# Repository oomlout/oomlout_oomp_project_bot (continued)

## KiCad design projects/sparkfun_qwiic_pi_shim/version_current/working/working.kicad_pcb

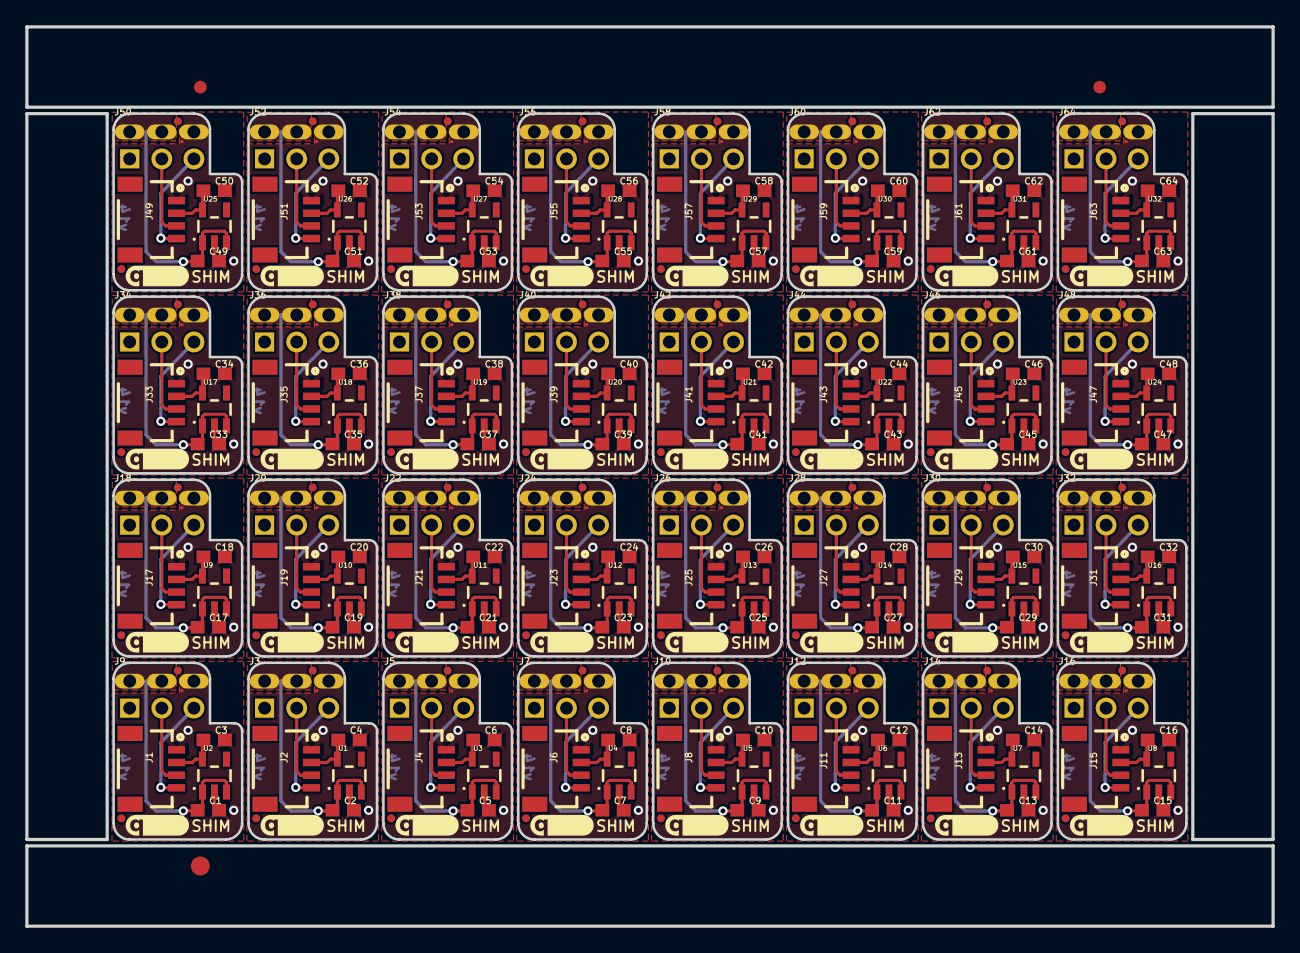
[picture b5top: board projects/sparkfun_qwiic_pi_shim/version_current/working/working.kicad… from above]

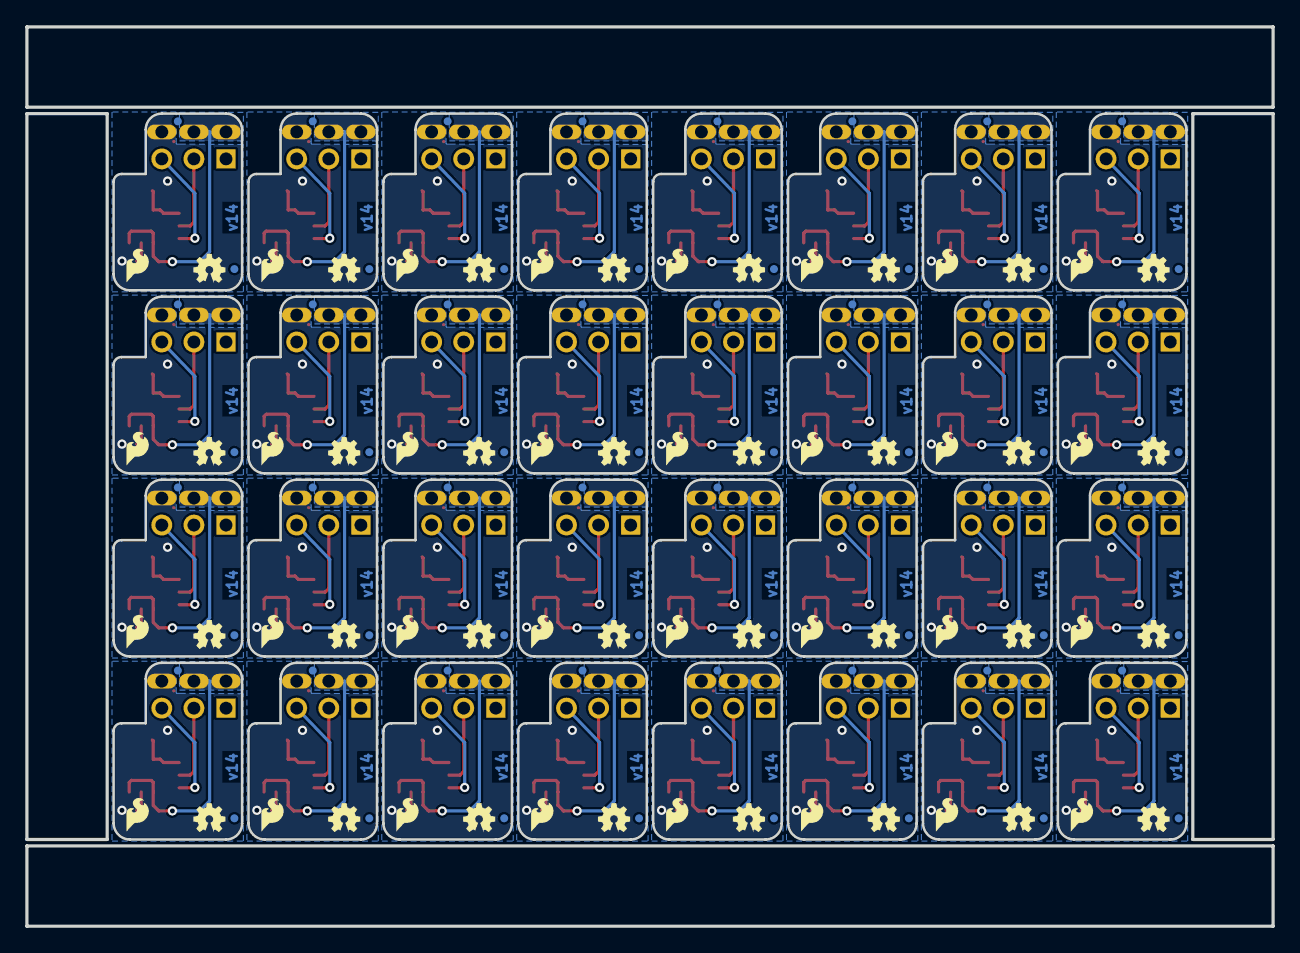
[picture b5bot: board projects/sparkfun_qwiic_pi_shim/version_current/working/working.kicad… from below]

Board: 2 copper layers, 98.6 x 71.1 mm, 387 parts (128 on the bottom side), 160 nets.

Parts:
C1, C2, C3, C4, C5, C6, C7, C8, C9, C10, C11, C12, C13, C14, C15, C16, C17, C18, C19, C20, C21, C22, C23, C24, C25, C26, C27, C28, C29, C30, C31, C32, C33, C34, C35, C36, C37, C38, C39, C40, C41, C42, C43, C44, C45, C46, C47, C48, C49, C50, C51, C52, C53, C54, C55, C56, C57, C58, C59, C60, C61, C62, C63, C64: 1.0uF; 0603
E$1, E$2: FIDUCIAL-1X2
E$3: FIDUCIAL-1.5X3
FD1, FD2, FD3, FD4, FD5, FD6, FD7, FD8, FD9, FD10, FD11, FD12, FD13, FD14, FD15, FD16, FD17, FD18, FD19, FD20, FD21, FD22, FD23, FD24, FD25, FD26, FD27, FD28, FD29, FD30, FD31, FD32, FD33, FD34, FD35, FD36, FD37, FD38, FD39, FD40, FD41, FD42, FD43, FD44, FD45, FD46, FD47, FD48, FD49, FD50, FD51, FD52, FD53, FD54, FD55, FD56, FD57, FD58, FD59, FD60, FD61, FD62, FD63, FD64, FD65, FD66, FD67, FD68, FD69, FD70, FD71, FD72, FD73, FD74, FD75, FD76, FD77, FD78, FD79, FD80, FD81, FD82, FD83, FD84, FD85, FD86, FD87, FD88, FD89, FD90, FD91, FD92, FD93, FD94, FD95, FD96, FD97, FD98, FD99, FD100, FD101, FD102, FD103, FD104, FD105, FD106, FD107, FD108, FD109, FD110, FD111, FD112, FD113, FD114, FD115, FD116, FD117, FD118, FD119, FD120, FD121, FD122, FD123, FD124, FD125, FD126, FD127, FD128: FIDUCIALUFIDUCIAL; FIDUCIAL-MICRO
J1, J2, J4, J6, J8, J11, J13, J15, J17, J19, J21, J23, J25, J27, J29, J31, J33, J35, J37, J39, J41, J43, J45, J47, J49, J51, J53, J55, J57, J59, J61, J63: Qwiic Right Angle; 1X04_1MM_RA
J3, J5, J7, J9, J10, J12, J14, J16, J18, J20, J22, J24, J26, J28, J30, J32, J34, J36, J38, J40, J42, J44, J46, J48, J50, J52, J54, J56, J58, J60, J62, J64: SPARKFUN-CONNECTORS_2X3-NS_PISHIM_LOCKING_SLOTS-4MILS
LOGO1, LOGO2, LOGO3, LOGO4, LOGO5, LOGO6, LOGO7, LOGO8, LOGO9, LOGO10, LOGO11, LOGO12, LOGO13, LOGO14, LOGO15, LOGO16, LOGO17, LOGO18, LOGO19, LOGO20, LOGO21, LOGO22, LOGO23, LOGO24, LOGO25, LOGO26, LOGO27, LOGO28, LOGO29, LOGO30, LOGO31, LOGO32: OSHW-LOGOMINI; OSHW-LOGO-MINI
U1, U2, U3, U4, U5, U6, U7, U8, U9, U10, U11, U12, U13, U14, U15, U16, U17, U18, U19, U20, U21, U22, U23, U24, U25, U26, U27, U28, U29, U30, U31, U32: 3.3V/600mA; SOT23-5
U$1, U$2, U$5, U$7, U$9, U$11, U$13, U$15, U$17, U$19, U$21, U$23, U$25, U$27, U$29, U$31, U$33, U$35, U$37, U$39, U$41, U$43, U$45, U$47, U$49, U$51, U$53, U$55, U$57, U$59, U$61, U$63: SFE_LOGO_FLAME.1_INCH; SFE_LOGO_FLAME_.1
U$3, U$4, U$6, U$8, U$10, U$12, U$14, U$16, U$18, U$20, U$22, U$24, U$26, U$28, U$30, U$32, U$34, U$36, U$38, U$40, U$42, U$44, U$46, U$48, U$50, U$52, U$54, U$56, U$58, U$60, U$62, U$64: QWIIC_5MM

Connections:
3.3V: C3.1, J1.2, U2.5
3.3V1: C4.1, J2.2, U1.5
3.3V2: C6.1, J4.2, U3.5
3.3V3: C8.1, J6.2, U4.5
3.3V4: C10.1, J8.2, U5.5
3.3V5: C12.1, J11.2, U6.5
3.3V6: C14.1, J13.2, U7.5
3.3V7: C16.1, J15.2, U8.5
3.3V8: C18.1, J17.2, U9.5
3.3V9: C20.1, J19.2, U10.5
3.3V10: C22.1, J21.2, U11.5
3.3V11: C24.1, J23.2, U12.5
3.3V12: C26.1, J25.2, U13.5
3.3V13: C28.1, J27.2, U14.5
3.3V14: C30.1, J29.2, U15.5
3.3V15: C32.1, J31.2, U16.5
3.3V16: C34.1, J33.2, U17.5
3.3V17: C36.1, J35.2, U18.5
3.3V18: C38.1, J37.2, U19.5
3.3V19: C40.1, J39.2, U20.5
3.3V20: C42.1, J41.2, U21.5
3.3V21: C44.1, J43.2, U22.5
3.3V22: C46.1, J45.2, U23.5
3.3V23: C48.1, J47.2, U24.5
3.3V24: C50.1, J49.2, U25.5
3.3V25: C52.1, J51.2, U26.5
3.3V26: C54.1, J53.2, U27.5
3.3V27: C56.1, J55.2, U28.5
3.3V28: C58.1, J57.2, U29.5
3.3V29: C60.1, J59.2, U30.5
3.3V30: C62.1, J61.2, U31.5
3.3V31: C64.1, J63.2, U32.5
5V: C1.1, J9.2, J9.4, U2.1, U2.3
5V1: C2.1, J3.2, J3.4, U1.1, U1.3
5V2: C5.1, J5.2, J5.4, U3.1, U3.3
5V3: C7.1, J7.2, J7.4, U4.1, U4.3
5V4: C9.1, J10.2, J10.4, U5.1, U5.3
5V5: C11.1, J12.2, J12.4, U6.1, U6.3
5V6: C13.1, J14.2, J14.4, U7.1, U7.3
5V7: C15.1, J16.2, J16.4, U8.1, U8.3
5V8: C17.1, J18.2, J18.4, U9.1, U9.3
5V9: C19.1, J20.2, J20.4, U10.1, U10.3
5V10: C21.1, J22.2, J22.4, U11.1, U11.3
5V11: C23.1, J24.2, J24.4, U12.1, U12.3
5V12: C25.1, J26.2, J26.4, U13.1, U13.3
5V13: C27.1, J28.2, J28.4, U14.1, U14.3
5V14: C29.1, J30.2, J30.4, U15.1, U15.3
5V15: C31.1, J32.2, J32.4, U16.1, U16.3
5V16: C33.1, J34.2, J34.4, U17.1, U17.3
5V17: C35.1, J36.2, J36.4, U18.1, U18.3
5V18: C37.1, J38.2, J38.4, U19.1, U19.3
5V19: C39.1, J40.2, J40.4, U20.1, U20.3
5V20: C41.1, J42.2, J42.4, U21.1, U21.3
5V21: C43.1, J44.2, J44.4, U22.1, U22.3
5V22: C45.1, J46.2, J46.4, U23.1, U23.3
5V23: C47.1, J48.2, J48.4, U24.1, U24.3
5V24: C49.1, J50.2, J50.4, U25.1, U25.3
5V25: C51.1, J52.2, J52.4, U26.1, U26.3
5V26: C53.1, J54.2, J54.4, U27.1, U27.3
5V27: C55.1, J56.2, J56.4, U28.1, U28.3
5V28: C57.1, J58.2, J58.4, U29.1, U29.3
5V29: C59.1, J60.2, J60.4, U30.1, U30.3
5V30: C61.1, J62.2, J62.4, U31.1, U31.3
5V31: C63.1, J64.2, J64.4, U32.1, U32.3
GND: C1.2, C3.2, J1.1, J9.6, U2.2
GND1: C2.2, C4.2, J2.1, J3.6, U1.2
GND2: C5.2, C6.2, J4.1, J5.6, U3.2
GND3: C7.2, C8.2, J6.1, J7.6, U4.2
GND4: C9.2, C10.2, J8.1, J10.6, U5.2
GND5: C11.2, C12.2, J11.1, J12.6, U6.2
GND6: C13.2, C14.2, J13.1, J14.6, U7.2
GND7: C15.2, C16.2, J15.1, J16.6, U8.2
GND8: C17.2, C18.2, J17.1, J18.6, U9.2
GND9: C19.2, C20.2, J19.1, J20.6, U10.2
GND10: C21.2, C22.2, J21.1, J22.6, U11.2
GND11: C23.2, C24.2, J23.1, J24.6, U12.2
GND12: C25.2, C26.2, J25.1, J26.6, U13.2
GND13: C27.2, C28.2, J27.1, J28.6, U14.2
GND14: C29.2, C30.2, J29.1, J30.6, U15.2
GND15: C31.2, C32.2, J31.1, J32.6, U16.2
GND16: C33.2, C34.2, J33.1, J34.6, U17.2
GND17: C35.2, C36.2, J35.1, J36.6, U18.2
GND18: C37.2, C38.2, J37.1, J38.6, U19.2
GND19: C39.2, C40.2, J39.1, J40.6, U20.2
GND20: C41.2, C42.2, J41.1, J42.6, U21.2
GND21: C43.2, C44.2, J43.1, J44.6, U22.2
GND22: C45.2, C46.2, J45.1, J46.6, U23.2
GND23: C47.2, C48.2, J47.1, J48.6, U24.2
GND24: C49.2, C50.2, J49.1, J50.6, U25.2
GND25: C51.2, C52.2, J51.1, J52.6, U26.2
GND26: C53.2, C54.2, J53.1, J54.6, U27.2
GND27: C55.2, C56.2, J55.1, J56.6, U28.2
GND28: C57.2, C58.2, J57.1, J58.6, U29.2
GND29: C59.2, C60.2, J59.1, J60.6, U30.2
GND30: C61.2, C62.2, J61.1, J62.6, U31.2
GND31: C63.2, C64.2, J63.1, J64.6, U32.2
SCL: J1.4, J9.5
SCL1: J2.4, J3.5
SCL2: J4.4, J5.5
SCL3: J6.4, J7.5
SCL4: J8.4, J10.5
SCL5: J11.4, J12.5
SCL6: J13.4, J14.5
SCL7: J15.4, J16.5
SCL8: J17.4, J18.5
SCL9: J19.4, J20.5
SCL10: J21.4, J22.5
SCL11: J23.4, J24.5
SCL12: J25.4, J26.5
SCL13: J27.4, J28.5
SCL14: J29.4, J30.5
SCL15: J31.4, J32.5
SCL16: J33.4, J34.5
SCL17: J35.4, J36.5
SCL18: J37.4, J38.5
SCL19: J39.4, J40.5
SCL20: J41.4, J42.5
SCL21: J43.4, J44.5
SCL22: J45.4, J46.5
SCL23: J47.4, J48.5
SCL24: J49.4, J50.5
SCL25: J51.4, J52.5
SCL26: J53.4, J54.5
SCL27: J55.4, J56.5
SCL28: J57.4, J58.5
SCL29: J59.4, J60.5
SCL30: J61.4, J62.5
SCL31: J63.4, J64.5
SDA: J1.3, J9.3
SDA1: J2.3, J3.3
SDA2: J4.3, J5.3
SDA3: J6.3, J7.3
SDA4: J8.3, J10.3
SDA5: J11.3, J12.3
SDA6: J13.3, J14.3
SDA7: J15.3, J16.3
SDA8: J17.3, J18.3
SDA9: J19.3, J20.3
SDA10: J21.3, J22.3
SDA11: J23.3, J24.3
SDA12: J25.3, J26.3
SDA13: J27.3, J28.3
SDA14: J29.3, J30.3
SDA15: J31.3, J32.3
SDA16: J33.3, J34.3
SDA17: J35.3, J36.3
SDA18: J37.3, J38.3
SDA19: J39.3, J40.3
SDA20: J41.3, J42.3
SDA21: J43.3, J44.3
SDA22: J45.3, J46.3
SDA23: J47.3, J48.3
SDA24: J49.3, J50.3
SDA25: J51.3, J52.3
SDA26: J53.3, J54.3
SDA27: J55.3, J56.3
SDA28: J57.3, J58.3
SDA29: J59.3, J60.3
SDA30: J61.3, J62.3
SDA31: J63.3, J64.3

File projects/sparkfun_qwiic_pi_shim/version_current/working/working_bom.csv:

"Id";"Designator";"Footprint";"Quantity";"Designation";"Supplier and ref";
1;"FD46,FD78,FD110,FD106,FD54,FD1,FD5,FD70,FD37,FD122,FD94,FD49,FD62,FD22,FD77,FD53,FD29,FD9,FD66,FD114,FD97,FD81,FD26,FD41,FD2,FD82,FD45,FD86,FD13,FD118,FD101,FD74,FD21,FD89,FD93,FD126,FD6,FD57,FD25,FD105,FD113,FD33,FD102,FD50,FD121,FD42,FD73,FD117,FD65,FD125,FD30,FD61,FD69,FD18,FD10,FD17,FD58,FD90,FD34,FD38,FD14,FD98,FD109,FD85,FD87,FD27,FD11,FD116,FD99,FD44,FD124,FD35,FD16,FD24,FD103,FD108,FD31,FD67,FD43,FD55,FD12,FD79,FD80,FD111,FD20,FD115,FD4,FD51,FD71,FD59,FD39,FD60,FD40,FD3,FD112,FD68,FD127,FD56,FD72,FD84,FD8,FD28,FD120,FD52,FD92,FD95,FD7,FD83,FD47,FD75,FD64,FD23,FD48,FD107,FD100,FD119,FD128,FD36,FD123,FD91,FD76,FD104,FD88,FD63,FD15,FD32,FD96,FD19";"FIDUCIAL-MICRO";128;"FIDUCIALUFIDUCIAL";;;
2;"C59,C39,C26,C11,C20,C19,C4,C1,C51,C6,C41,C31,C29,C32,C14,C46,C15,C52,C43,C21,C8,C9,C18,C56,C40,C49,C12,C17,C58,C5,C35,C2,C57,C50,C33,C23,C45,C7,C30,C38,C3,C28,C34,C64,C60,C47,C48,C55,C61,C10,C63,C44,C62,C37,C27,C42,C54,C53,C36,C22,C24,C25,C16,C13";"0603";64;"1.0uF";;;
3;"J27,J61,J37,J8,J55,J19,J29,J49,J53,J63,J35,J11,J41,J45,J25,J43,J59,J33,J6,J2,J23,J31,J47,J1,J13,J15,J21,J4,J17,J39,J57,J51";"1X04_1MM_RA";32;"Qwiic Right Angle";;;
4;"U$14,U$40,U$62,U$26,U$6,U$64,U$34,U$30,U$50,U$3,U$32,U$12,U$42,U$56,U$38,U$18,U$8,U$4,U$44,U$24,U$46,U$54,U$28,U$60,U$20,U$58,U$36,U$16,U$52,U$48,U$10,U$22";"QWIIC_5MM";32;"";;;
5;"U20,U31,U25,U12,U29,U4,U10,U30,U7,U6,U9,U19,U24,U5,U16,U28,U17,U18,U32,U21,U26,U13,U8,U1,U27,U3,U14,U15,U23,U22,U11,U2";"SOT23-5";32;"3.3V/600mA";;;
6;"J30,J28,J44,J48,J36,J3,J62,J60,J24,J16,J40,J34,J10,J58,J64,J9,J5,J12,J46,J32,J22,J52,J14,J7,J56,J50,J18,J26,J20,J38,J54,J42";"SPARKFUN-CONNECTORS_2X3-NS_PISHIM_LOCKING_SLOTS-4MILS";32;"";;;
7;"E$1,E$2";"FIDUCIAL-1X2";2;"";;;
8;"E$3";"FIDUCIAL-1.5X3";1;"";;;
9;"LOGO18,LOGO13,LOGO32,LOGO19,LOGO1,LOGO27,LOGO14,LOGO12,LOGO30,LOGO21,LOGO4,LOGO5,LOGO8,LOGO11,LOGO15,LOGO23,LOGO9,LOGO20,LOGO6,LOGO17,LOGO24,LOGO28,LOGO31,LOGO3,LOGO7,LOGO16,LOGO2,LOGO29,LOGO10,LOGO25,LOGO26,LOGO22";"OSHW-LOGO-MINI";32;"OSHW-LOGOMINI";;;
10;"U$11,U$45,U$19,U$29,U$47,U$2,U$49,U$13,U$43,U$1,U$37,U$61,U$33,U$41,U$7,U$53,U$17,U$57,U$5,U$9,U$39,U$51,U$63,U$15,U$21,U$23,U$31,U$59,U$55,U$27,U$35,U$25";"SFE_LOGO_FLAME_.1";32;"SFE_LOGO_FLAME.1_INCH";;;

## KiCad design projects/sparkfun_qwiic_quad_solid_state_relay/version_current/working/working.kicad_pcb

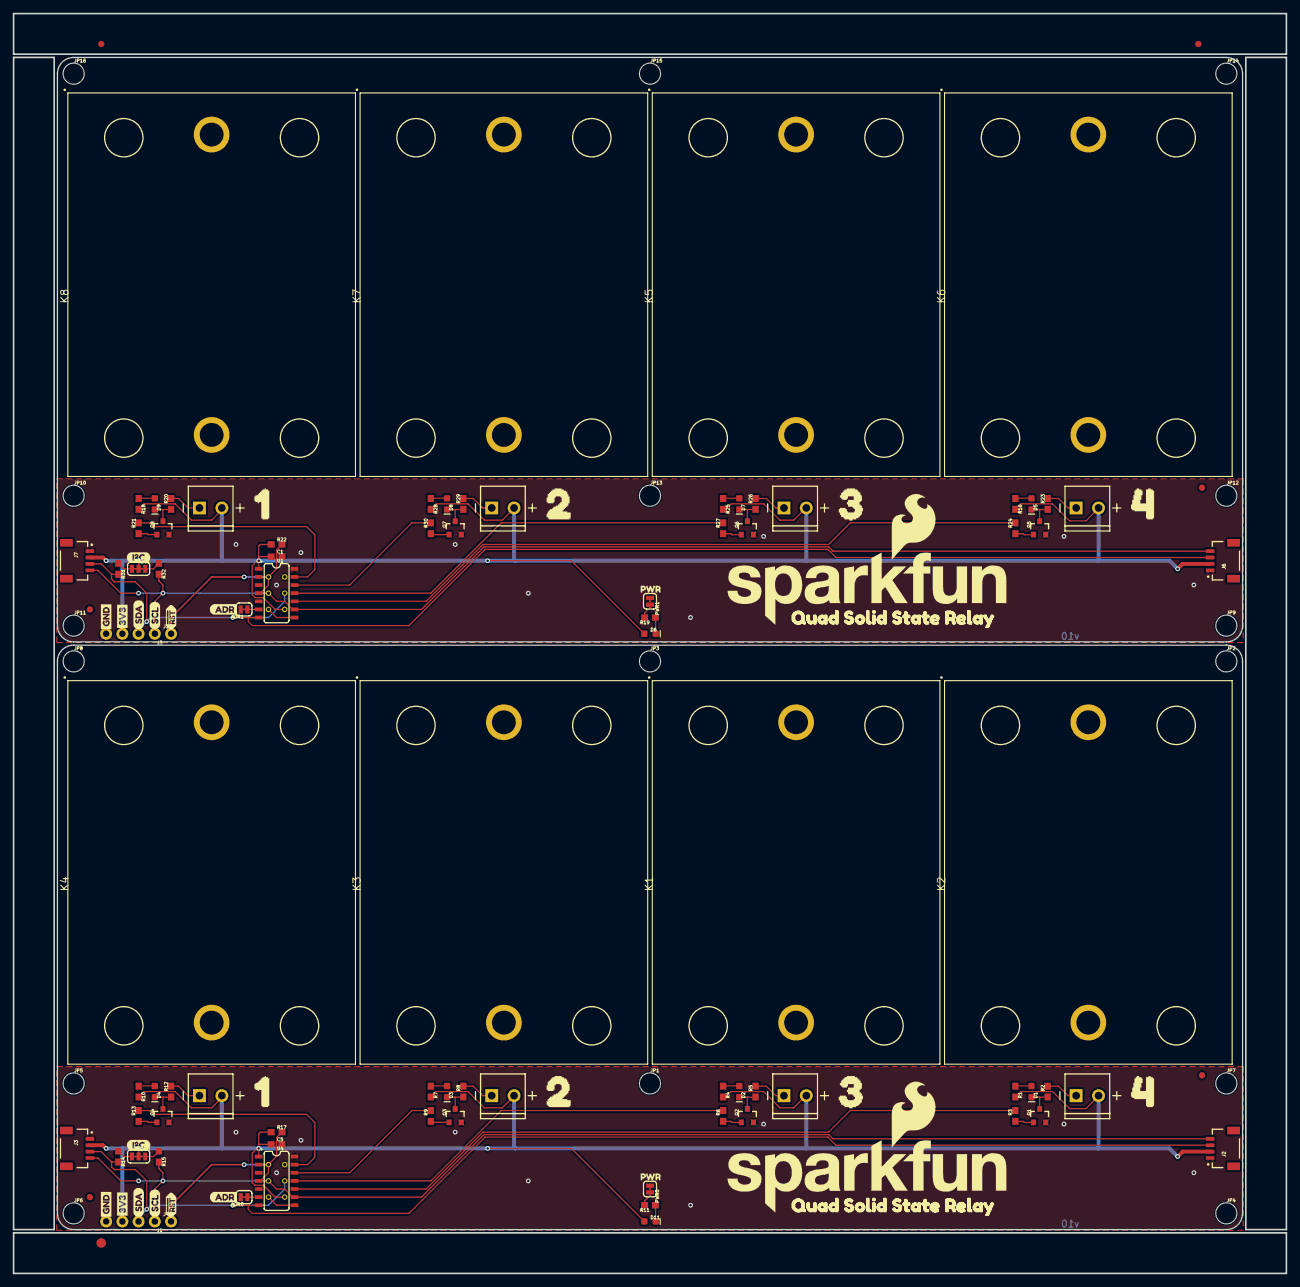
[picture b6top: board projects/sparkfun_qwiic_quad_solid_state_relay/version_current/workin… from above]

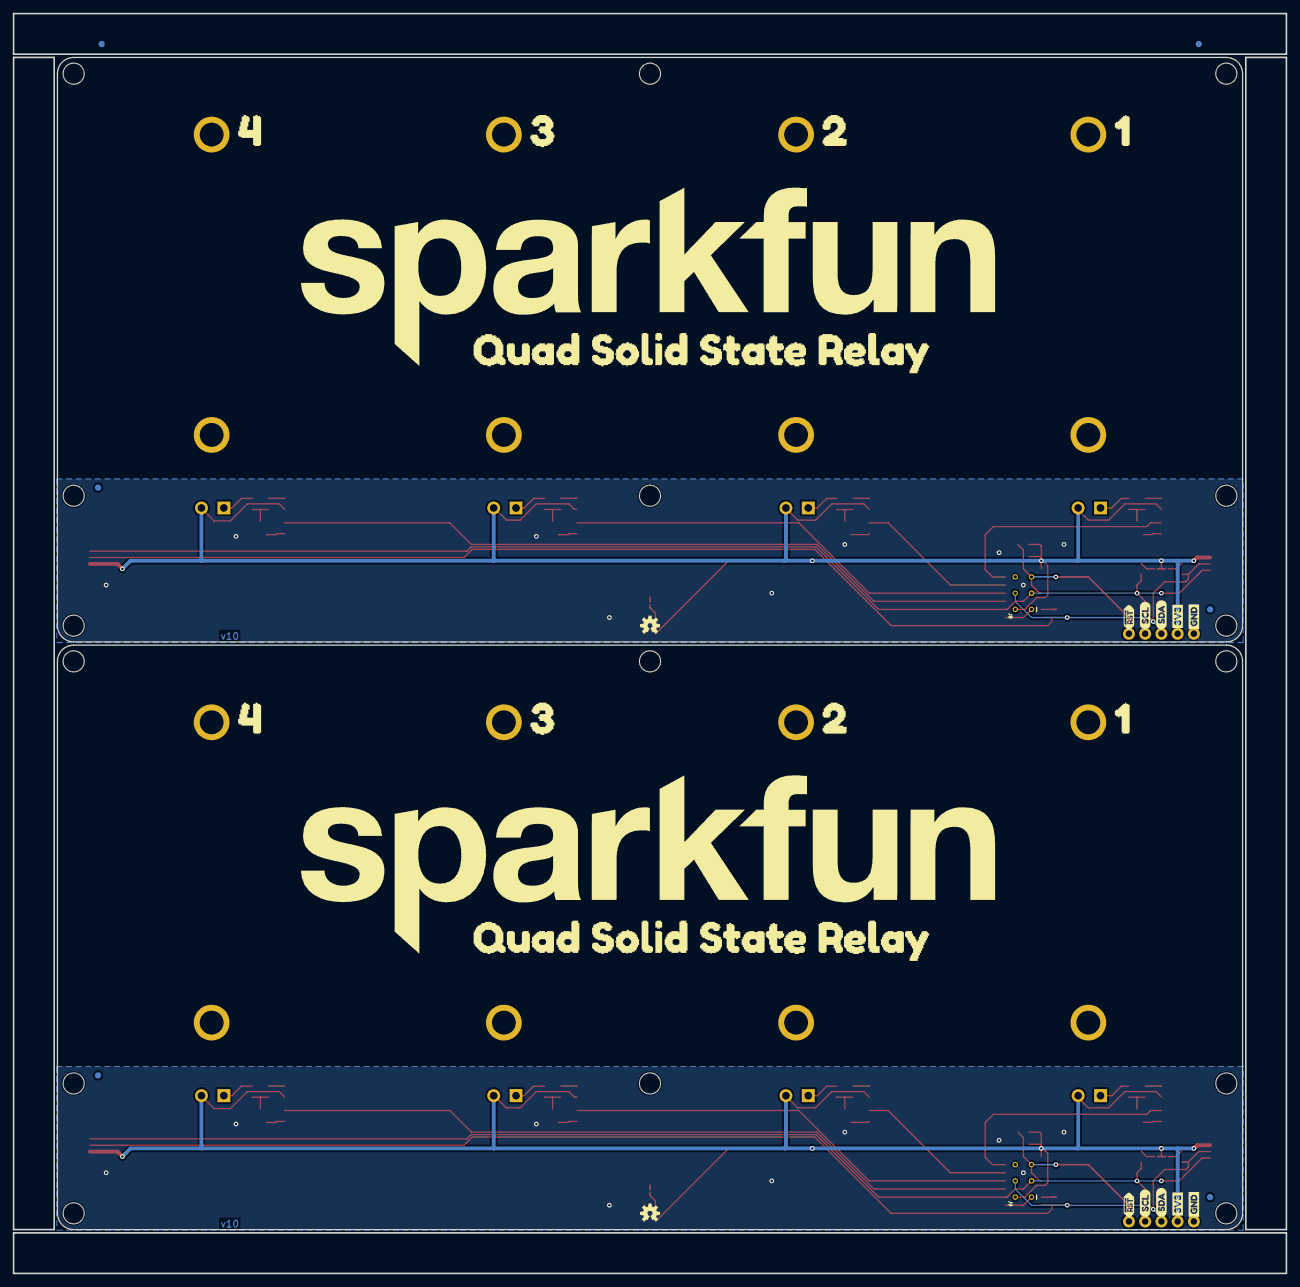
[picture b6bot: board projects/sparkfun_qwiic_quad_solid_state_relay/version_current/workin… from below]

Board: 2 copper layers, 199.1 x 197.1 mm, 161 parts (32 on the bottom side), 62 nets.

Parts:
ADR0, ADR1: JUMPER-SMT_2_NC_TRACE_SILK; SMT-JUMPER_2_NC_TRACE_SILK
C1, C5: 0.1uF; 0603
D1, D2, D3, D4, D5, D7, D8, D9: BLUE; LED-0603
D6, D11: RED; LED-0603
E$1, E$2, E$3, E$4: FIDUCIAL-1X2
E$5: FIDUCIAL-1.5X3
FD1, FD2, FD3, FD4, FD5, FD6, FD7, FD8: FIDUCIAL1X2; FIDUCIAL-1X2
I2C0, I2C1: JUMPER-SMT_3_2-NC_TRACE_SILK; SMT-JUMPER_3_2-NC_TRACE_SILK
J1, J5: 1X04_NO_SILK
J2, J3, J6, J7: Qwiic Right Angle; JST04_1MM_RA
J4, J10: 1X01_NO_SILK
J8, J9: AVR_SPI_PROG_3X2TESTPOINTS; 2X3_TEST_POINTS
JP1, JP2, JP3, JP4, JP5, JP6, JP7, JP8, JP9, JP10, JP11, JP12, JP13, JP14, JP15, JP16: STAND-OFF
K1, K2, K3, K4, K5, K6, K7, K8: Solid State Relay - 40A; SSR-40DA-H
LOGO1, LOGO4: SFE_LOGO_NAME1_INCH; SFE_LOGO_NAME_1
LOGO2, LOGO3: OSHW-LOGOS; OSHW-LOGO-S
PWR0, PWR1: JUMPER-SMT_2_NC_TRACE_SILK; SMT-JUMPER_2_NC_TRACE_SILK
Q1, Q2, Q3, Q4, Q5, Q6, Q7, Q8: 600mA/40V; SOT23-3
R1, R3, R4, R6, R7, R9, R10, R11, R13, R16, R18, R19, R21, R24, R25, R27, R28, R30: 1k; 0603
R2, R5, R8, R12, R20, R23, R26, R29: 47; 0603
R14, R15, R17, R22, R31, R32: 4.7k; 0603
U1, U4: ATTINY84-ARDUINO; SO14
U$1, U$26: SFE_LOGO_NAME_FLAME_.4
U$2, U$3, U$4, U$27, U$28, U$29: QUAD_SOLID_STATE_RELAY0
U$5, U$9, U$30, U$34: 11
U$6, U$10, U$31, U$35: 22
U$7, U$11, U$32, U$36: 33
U$8, U$12, U$33, U$37: 44
U$13, U$14, U$38, U$39: GND_P
U$15, U$40: I2C
U$16, U$17, U$41, U$42: 3V3_P
U$18, U$19, U$43, U$44: SCL_IO
U$20, U$21, U$45, U$46: SDA_IO
U$22, U$47: PWR_TO
U$23, U$48: ADR3
U$24, U$25, U$49, U$50: !RST_I

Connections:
3.3V: C5.1, D11.A, I2C0.2, J1.3, J2.2, J3.2, J9.2, K1.2, K2.2, K3.2, K4.2, R1.2, R4.2, R7.2, R10.2, R17.1, U4.1
3.3V1: C1.1, D6.A, I2C1.2, J5.3, J6.2, J7.2, J8.2, K5.2, K6.2, K7.2, K8.2, R16.2, R18.2, R22.1, R25.2, R28.2, U1.1
ADDR_JUMP: ADR0.1, U4.6
ADDR_JUMP1: ADR1.1, U1.6
GND: ADR0.2, C5.2, J1.4, J2.1, J3.1, J9.6, PWR0.1, Q1.2, Q2.2, Q3.2, Q4.2, U4.14
GND1: ADR1.2, C1.2, J5.4, J6.1, J7.1, J8.6, PWR1.1, Q5.2, Q6.2, Q7.2, Q8.2, U1.14
MISO: J9.1, U4.8
MISO1: J8.1, U1.8
unnamed: D2.C, Q2.3, R5.1
unnamed: D1.C, Q1.3, R2.1
unnamed: K1.1, R5.2
unnamed: D2.A, R4.1
unnamed: D3.C, Q3.3, R8.1
unnamed: K3.1, R8.2
unnamed: D1.A, R1.1
unnamed: D3.A, R7.1
unnamed: D4.C, Q4.3, R12.1
unnamed: K2.1, R2.2
unnamed: K4.1, R12.2
unnamed: D4.A, R10.1
unnamed: D11.C, R11.1
unnamed: PWR0.2, R11.2
unnamed: I2C0.3, R15.1
unnamed: I2C0.1, R14.1
unnamed: D6.C, R19.1
unnamed: PWR1.2, R19.2
unnamed: D5.C, Q5.3, R23.1
unnamed: K6.1, R23.2
unnamed: D5.A, R16.1
unnamed: D7.C, Q6.3, R26.1
unnamed: K5.1, R26.2
unnamed: D7.A, R25.1
unnamed: D8.C, Q7.3, R29.1
unnamed: K7.1, R29.2
unnamed: D8.A, R28.1
unnamed: D9.C, Q8.3, R20.1
unnamed: K8.1, R20.2
unnamed: D9.A, R18.1
unnamed: I2C1.3, R32.1
unnamed: I2C1.1, R31.1
OPTO_1: Q1.1, R3.1
OPTO_2: Q2.1, R6.1
OPTO_3: Q3.1, R9.1
OPTO_4: Q4.1, R13.1
OPTO_5: Q5.1, R24.1
OPTO_6: Q6.1, R27.1
OPTO_7: Q7.1, R30.1
OPTO_8: Q8.1, R21.1
RELAY_CTRL1: R3.2, U4.10
RELAY_CTRL2: R6.2, U4.11
RELAY_CTRL3: R9.2, U4.12
RELAY_CTRL4: R13.2, U4.13
RELAY_CTRL5: R24.2, U1.10
RELAY_CTRL6: R27.2, U1.11
RELAY_CTRL7: R30.2, U1.12
RELAY_CTRL8: R21.2, U1.13
SCL/SCK: J1.1, J2.4, J3.4, J9.3, R15.2, U4.9
SCL/SCK1: J5.1, J6.4, J7.4, J8.3, R32.2, U1.9
SDA/MOSI: J1.2, J2.3, J3.3, J9.4, R14.2, U4.7
SDA/MOSI1: J5.2, J6.3, J7.3, J8.4, R31.2, U1.7
~RESET1: J8.5, J10.1, R22.2, U1.4
~RESET: J4.1, J9.5, R17.2, U4.4

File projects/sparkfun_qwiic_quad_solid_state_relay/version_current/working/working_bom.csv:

"Id";"Designator";"Footprint";"Quantity";"Designation";"Supplier and ref";
1;"Q7,Q3,Q4,Q1,Q8,Q6,Q2,Q5";"SOT23-3";8;"600mA/40V";;;
2;"D9,D3,D5,D8,D7,D4,D2,D1";"LED-0603";8;"BLUE";;;
3;"JP10,JP8,JP14,JP9,JP5,JP3,JP16,JP6,JP1,JP15,JP12,JP7,JP4,JP2,JP13,JP11";"STAND-OFF";16;"STAND-OFF";;;
4;"J10,J4";"1X01_NO_SILK";2;"";;;
5;"FD5,FD1,FD8,FD4,FD2,FD3,FD6,FD7";"FIDUCIAL-1X2";8;"FIDUCIAL1X2";;;
6;"K8,K2,K4,K7,K1,K6,K5,K3";"SSR-40DA-H";8;"Solid State Relay - 40A";;;
7;"R21,R16,R1,R30,R25,R9,R18,R6,R13,R3,R4,R7,R11,R19,R10,R27,R24,R28";"0603";18;"1k";;;
8;"U$26,U$1";"SFE_LOGO_NAME_FLAME_.4";2;"";;;
9;"U$48,U$23";"ADR3";2;"";;;
10;"D11,D6";"LED-0603";2;"RED";;;
11;"PWR1,PWR0,ADR0,ADR1";"SMT-JUMPER_2_NC_TRACE_SILK";4;"JUMPER-SMT_2_NC_TRACE_SILK";;;
12;"J7,J2,J6,J3";"JST04_1MM_RA";4;"Qwiic Right Angle";;;
13;"U$30,U$5,U$9,U$34";"11";4;"";;;
14;"U$20,U$45,U$21,U$46";"SDA_IO";4;"";;;
15;"U$15,U$40";"I2C";2;"";;;
16;"R31,R14,R17,R22,R32,R15";"0603";6;"4.7k";;;
17;"I2C0,I2C1";"SMT-JUMPER_3_2-NC_TRACE_SILK";2;"JUMPER-SMT_3_2-NC_TRACE_SILK";;;
18;"U$3,U$4,U$28,U$27,U$2,U$29";"QUAD_SOLID_STATE_RELAY0";6;"";;;
19;"U4,U1";"SO14";2;"ATTINY84-ARDUINO";;;
20;"C1,C5";"0603";2;"0.1uF";;;
21;"U$6,U$31,U$10,U$35";"22";4;"";;;
22;"U$33,U$8,U$37,U$12";"44";4;"";;;
23;"J5,J1";"1X04_NO_SILK";2;"";;;
24;"U$24,U$49,U$50,U$25";"!RST_I";4;"";;;
25;"U$22,U$47";"PWR_TO";2;"";;;
26;"U$43,U$18,U$19,U$44";"SCL_IO";4;"";;;
27;"R23,R12,R20,R26,R5,R8,R29,R2";"0603";8;"47";;;
28;"E$1,E$3,E$2,E$4";"FIDUCIAL-1X2";4;"";;;
29;"U$38,U$13,U$39,U$14";"GND_P";4;"";;;
30;"U$41,U$16,U$17,U$42";"3V3_P";4;"";;;
31;"U$32,U$7,U$36,U$11";"33";4;"";;;
32;"E$5";"FIDUCIAL-1.5X3";1;"";;;
33;"LOGO3,LOGO2";"OSHW-LOGO-S";2;"OSHW-LOGOS";;;
34;"LOGO4,LOGO1";"SFE_LOGO_NAME_1";2;"SFE_LOGO_NAME1_INCH";;;
35;"J9,J8";"2X3_TEST_POINTS";2;"AVR_SPI_PROG_3X2TESTPOINTS";;;

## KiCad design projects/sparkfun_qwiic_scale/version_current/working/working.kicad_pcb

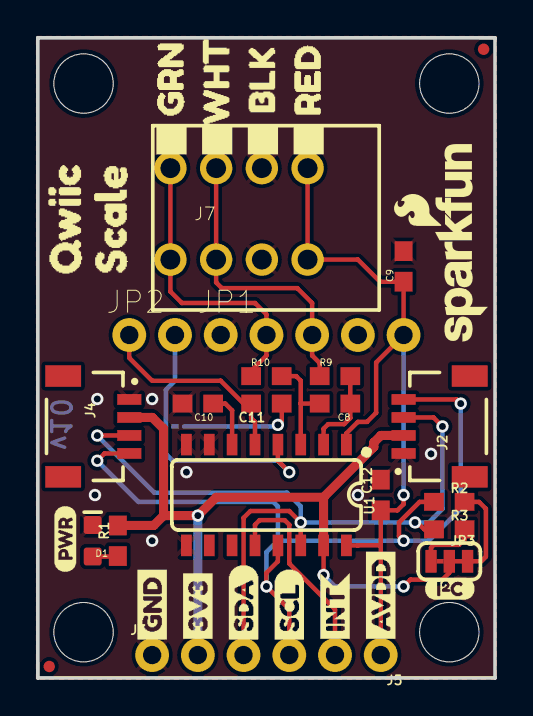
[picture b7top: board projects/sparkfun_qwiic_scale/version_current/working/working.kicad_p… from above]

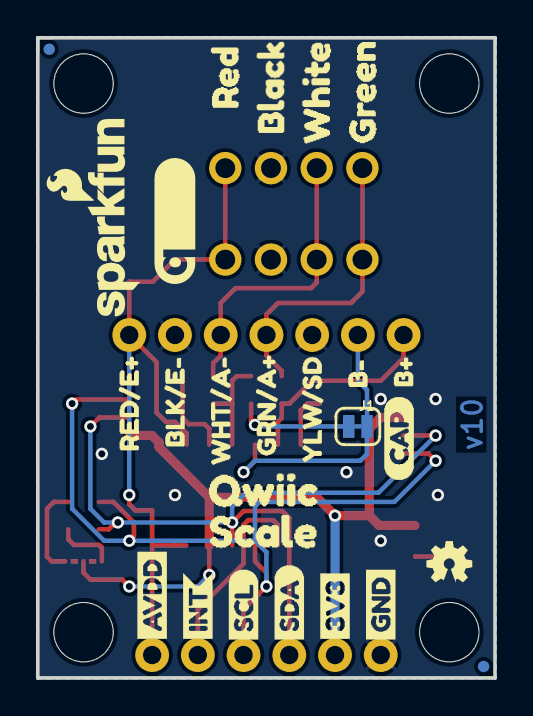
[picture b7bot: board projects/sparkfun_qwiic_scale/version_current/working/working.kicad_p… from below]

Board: 2 copper layers, 25.4 x 35.6 mm, 68 parts (26 on the bottom side), 17 nets.

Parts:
C8, C9, C10: 0.1uF; 0603
C11: 330pF; 0603
C12: 1.0uF; 0603
D1: RED; LED-0603
FRAME1: FRAME-LETTER; CREATIVE_COMMONS
J1: CAP; SMT-JUMPER_2_NC_TRACE_SILK
J2, J4: Qwiic Right Angle; JST04_1MM_RA
J3: PTH; 1X04_NO_SILK
J5: 1X02_NO_SILK
J7: Spring Terminal; 1X04_SPRING_TERMINAL
JP1: 1X05_NO_SILK
JP2: 1X02_NO_SILK
JP3: I2C; SMT-JUMPER_3_2-NC_TRACE_SILK
JP21, JP61, JP71, JP81: FIDUCIALUFIDUCIAL; MICRO-FIDUCIAL
JP31, JP41, JP91, JP101: STAND-OFF
LOGO1: OSHW-LOGOMINI; OSHW-LOGO-MINI
LOGO2, LOGO3: SFE_LOGO_NAME_FLAME.1_INCH; SFE_LOGO_NAME_FLAME_.1
R1: 1k; 0603
R2, R3: 2.2k; 0603
R9, R10: 47; 0603
U1: NAU7802; SO16
U$1, U$4: SDA-[)
U$3, U$5: SCL-[)
U$6, U$7: 3V3-04
U$8, U$9: GND-04
U$11: YLW#SD4
U$12: B#11
U$13: B#12
U$14, U$22: QWIIC2
U$15, U$21: INT0
U$16: QWIIC_LOGO_7MM; QWIIC_7MM
U$17, U$24: SCALE3
U$18: PWR-()-03
U$19: I_SUPER2_C-()-03
U$20: CAP0
U$34: BLK#E#1
U$35: GRN#A#4
U$36, U$45: AVDD4
U$37: BLACK5
U$38: BLK1
U$39: GREEN7
U$40: GRN3
U$41: RED0
U$42: RED4
U$43: WHITE6
U$44: WHT2
U$46: RED#E#2
U$48: WHT#A#3

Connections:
3.3V: J2.2, J3.2, J4.2, JP3.2, R1.2, U1.15
A+: J7.4, J7.8, JP1.2, R10.1
A-: J7.3, J7.7, JP1.3, R9.1
B+: C11.2, JP2.1, U1.5
B-: J1.2, JP2.2, U1.4
GND: C9.2, C10.2, C12.2, D1.C, J2.1, J3.1, J4.1, J7.2, J7.6, JP1.1, JP1.4, U1.7, U1.8, U1.9
INT: J5.2, U1.12
unnamed: C11.1, J1.1
unnamed: JP3.1, R3.2
unnamed: JP3.3, R2.2
unnamed: D1.A, R1.1
unnamed: C10.1, U1.6
unnamed: C8.2, R10.2, U1.3
unnamed: C8.1, R9.2, U1.2
SCL: J2.4, J3.4, J4.4, R2.1, U1.13
SDA: J2.3, J3.3, J4.3, R3.1, U1.14
VDDA: C9.1, C12.1, J5.1, J7.1, J7.5, JP1.5, U1.1, U1.16

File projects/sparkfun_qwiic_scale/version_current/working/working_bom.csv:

"Id";"Designator";"Footprint";"Quantity";"Designation";"Supplier and ref";
1;"JP101,JP41,JP91,JP31";"STAND-OFF";4;"STAND-OFF";;;
2;"U$21,U$15";"INT0";2;"";;;
3;"U$3,U$5";"SCL-[)";2;"";;;
4;"U$38";"BLK1";1;"";;;
5;"J3";"1X04_NO_SILK";1;"PTH";;;
6;"U$18";"PWR-()-03";1;"";;;
7;"U$24,U$17";"SCALE3";2;"";;;
8;"U$1,U$4";"SDA-[)";2;"";;;
9;"C11";"0603";1;"330pF";;;
10;"FRAME1";"CREATIVE_COMMONS";1;"FRAME-LETTER";;;
11;"JP3";"SMT-JUMPER_3_2-NC_TRACE_SILK";1;"I2C";;;
12;"JP2,J5";"1X02_NO_SILK";2;"";;;
13;"C10,C9,C8";"0603";3;"0.1uF";;;
14;"LOGO3,LOGO2";"SFE_LOGO_NAME_FLAME_.1";2;"SFE_LOGO_NAME_FLAME.1_INCH";;;
15;"J2,J4";"JST04_1MM_RA";2;"Qwiic Right Angle";;;
16;"D1";"LED-0603";1;"RED";;;
17;"R3,R2";"0603";2;"2.2k";;;
18;"R1";"0603";1;"1k";;;
19;"U$40";"GRN3";1;"";;;
20;"U$8,U$9";"GND-04";2;"";;;
21;"C12";"0603";1;"1.0uF";;;
22;"JP1";"1X05_NO_SILK";1;"";;;
23;"U1";"SO16";1;"NAU7802";;;
24;"R10,R9";"0603";2;"47";;;
25;"J7";"1X04_SPRING_TERMINAL";1;"Spring Terminal";;;
26;"U$41";"RED0";1;"";;;
27;"JP21,JP61,JP71,JP81";"MICRO-FIDUCIAL";4;"FIDUCIALUFIDUCIAL";;;
28;"U$44";"WHT2";1;"";;;
29;"U$19";"I_SUPER2_C-()-03";1;"";;;
30;"U$36,U$45";"AVDD4";2;"";;;
31;"U$6,U$7";"3V3-04";2;"";;;
32;"U$22,U$14";"QWIIC2";2;"";;;
33;"U$11";"YLW#SD4";1;"";;;
34;"U$43";"WHITE6";1;"";;;
35;"LOGO1";"OSHW-LOGO-MINI";1;"OSHW-LOGOMINI";;;
36;"U$46";"RED#E#2";1;"";;;
37;"U$16";"QWIIC_7MM";1;"QWIIC_LOGO_7MM";;;
38;"U$35";"GRN#A#4";1;"";;;
39;"J1";"SMT-JUMPER_2_NC_TRACE_SILK";1;"CAP";;;
40;"U$34";"BLK#E#1";1;"";;;
41;"U$37";"BLACK5";1;"";;;
42;"U$12";"B#11";1;"";;;
43;"U$48";"WHT#A#3";1;"";;;
44;"U$13";"B#12";1;"";;;
45;"U$42";"RED4";1;"";;;
46;"U$20";"CAP0";1;"";;;
47;"U$39";"GREEN7";1;"";;;

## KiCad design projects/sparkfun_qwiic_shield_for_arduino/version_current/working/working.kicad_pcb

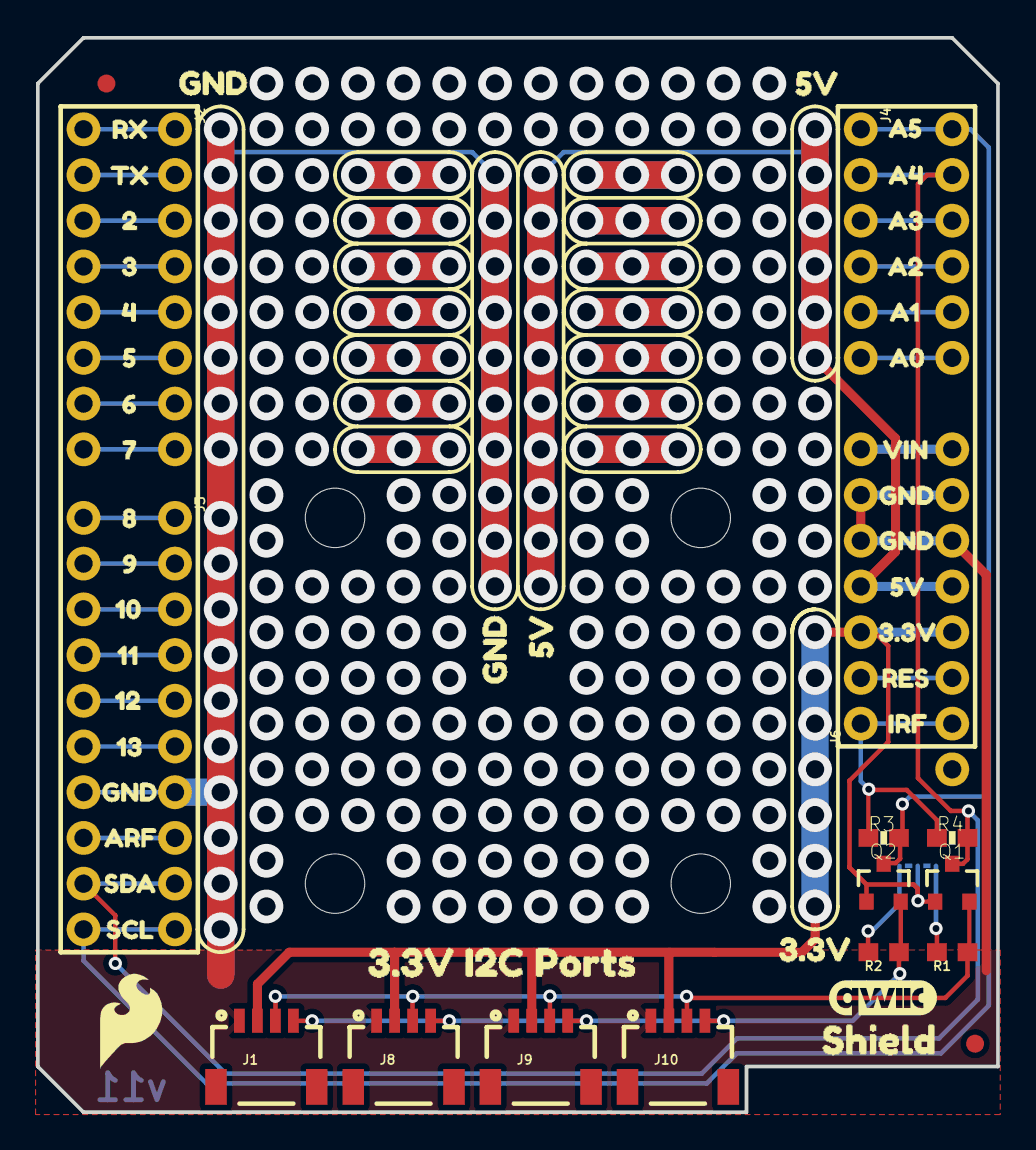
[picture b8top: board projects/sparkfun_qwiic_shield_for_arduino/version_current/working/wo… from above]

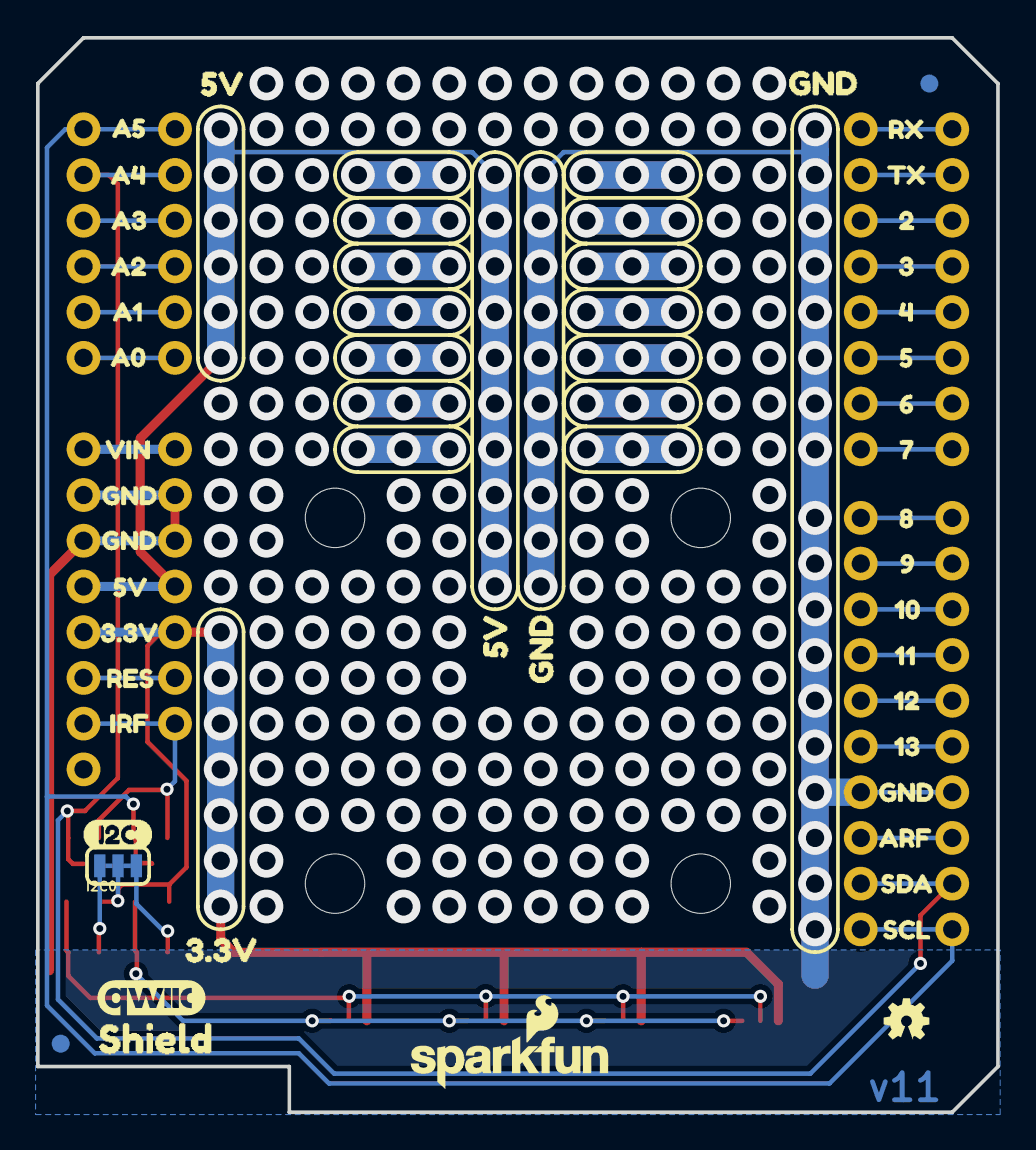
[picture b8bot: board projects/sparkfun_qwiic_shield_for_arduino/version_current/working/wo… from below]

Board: 2 copper layers, 53.3 x 59.7 mm, 104 parts (44 on the bottom side), 31 nets.

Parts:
FD1, FD2, FD3, FD4: FIDUCIAL1X2; FIDUCIAL-1X2
FRAME1: FRAME-LETTER; CREATIVE_COMMONS
I2C0: SMT-JUMPER_3_2-NC_TRACE_SILK
J1, J8, J9, J10: Qwiic Right Angle; 1X04_1MM_RA
J2: 1X08_NO_SILK
J3: 1X10_NO_SILK
J4: 1X06_NO_SILK
J6: 1X07_NO_SILK
LOGO1: OSHW-LOGOMINI; OSHW-LOGO-MINI
LOGO2: REVISION
LOGO3, LOGO4: QWIIC_LOGO_6MM; QWIIC_6MM
Q1, Q2: BSS138; SOT23-3
R1, R2: 4.7k; 0603
R3, R4: 4.7K; 0603-RES
U1: ARDUINO UNO; UNO_R3_SHIELD_NOLABELS
U$1: SFE_LOGO_FLAME_.2
U$2: SFE_LOGO_NAME_FLAME.1_INCH; SFE_LOGO_NAME_FLAME_.1
U$3: QWIIC_BOARD_OUTLINEH; QWIIC_BOARD_MOUNT_HOLES
U$4, U$5: SHIELD0
U$6: 3#3V_I2C_PORTS1
U$7, U$8: RX5
U$9, U$10: TX6
U$11, U$12: 27
U$13, U$14: 38
U$15, U$16: 49
U$17, U$18: 510
U$19, U$20: 611
U$21, U$23: 712
U$22: I2C0
U$24, U$25: 813
U$26, U$27: 914
U$28, U$29: 1015
U$30, U$31: 1116
U$32, U$33: 1217
U$34, U$35: 1318
U$36, U$37, U$68, U$69, U$70, U$71: GND30
U$38, U$39: ARF20
U$40, U$41: SDA21
U$42, U$43: SCL22
U$44, U$45, U$46, U$47: GND2
U$48, U$49: 3#3V4
U$50, U$51, U$52, U$53: 5V3
U$54, U$55: A523
U$56, U$57: A424
U$58, U$59: A325
U$60, U$61: A226
U$62, U$63: A127
U$64, U$65: A028
U$66, U$67: VIN29
U$72, U$73: 5V31
U$74, U$75: 3#3V32
U$76, U$77: RES33
U$78, U$79: IRF34

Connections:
3.3V: I2C0.2, J1.2, J6.3, J8.2, J9.2, J10.2, Q1.1, Q2.1, U1.3.3V
5V: J6.4, U1.5V
A0: J4.6, U1.A0
A1: J4.5, U1.A1
A2: J4.4, U1.A2
A3: J4.3, U1.A3
AREF: J3.8, U1.AREF
D2: J2.3, U1.D2
D3: J2.4, U1.D3
D4: J2.5, U1.D4
D5: J2.6, U1.D5
D6: J2.7, U1.D6
D7: J2.8, U1.D7
D8: J3.1, U1.D8
D9: J3.2, U1.D9
D10: J3.3, U1.D10
D11: J3.4, U1.D11
D12: J3.5, U1.D12
D13: J3.6, U1.D13
GND: J1.1, J3.7, J6.5, J6.6, J8.1, J9.1, J10.1, U1.GND@0, U1.GND@1, U1.GND@2
IOREF: J6.1, R3.1, R4.1, U1.IOREF
unnamed: I2C0.3, R1.2
unnamed: I2C0.1, R2.2
RES: J6.2, U1.RES
RX: J2.1, U1.RX
SCL: J1.4, J8.4, J9.4, J10.4, Q2.2, R2.1
SCL_R3: J3.10, J4.1, Q2.3, R3.2, U1.A5, U1.SCL
SDA: J1.3, J8.3, J9.3, J10.3, Q1.2, R1.1
SDA_R3: J3.9, J4.2, Q1.3, R4.2, U1.A4, U1.SDA
TX: J2.2, U1.TX
VIN: J6.7, U1.VIN

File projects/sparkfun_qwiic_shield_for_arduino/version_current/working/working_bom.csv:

"Id";"Designator";"Footprint";"Quantity";"Designation";"Supplier and ref";
1;"Q1,Q2";"SOT23-3";2;"BSS138";;;
2;"U$43,U$42";"SCL22";2;"";;;
3;"U$15,U$16";"49";2;"";;;
4;"U$74,U$75";"3#3V32";2;"";;;
5;"FD2,FD1,FD3,FD4";"FIDUCIAL-1X2";4;"FIDUCIAL1X2";;;
6;"U$35,U$34";"1318";2;"";;;
7;"J10,J1,J8,J9";"1X04_1MM_RA";4;"Qwiic Right Angle";;;
8;"U$31,U$30";"1116";2;"";;;
9;"FRAME1";"CREATIVE_COMMONS";1;"FRAME-LETTER";;;
10;"U$11,U$12";"27";2;"";;;
11;"U$10,U$9";"TX6";2;"";;;
12;"U$57,U$56";"A424";2;"";;;
13;"R4,R3";"0603-RES";2;"4.7K";;;
14;"R2,R1";"0603";2;"4.7k";;;
15;"J2";"1X08_NO_SILK";1;"";;;
16;"U$58,U$59";"A325";2;"";;;
17;"U$50,U$52,U$53,U$51";"5V3";4;"";;;
18;"U$46,U$44,U$45,U$47";"GND2";4;"";;;
19;"U$27,U$26";"914";2;"";;;
20;"U$18,U$17";"510";2;"";;;
21;"U$73,U$72";"5V31";2;"";;;
22;"U$19,U$20";"611";2;"";;;
23;"LOGO2";"REVISION";1;"REVISION";;;
24;"U$65,U$64";"A028";2;"";;;
25;"J3";"1X10_NO_SILK";1;"";;;
26;"U$14,U$13";"38";2;"";;;
27;"LOGO3,LOGO4";"QWIIC_6MM";2;"QWIIC_LOGO_6MM";;;
28;"U$78,U$79";"IRF34";2;"";;;
29;"U$28,U$29";"1015";2;"";;;
30;"U$66,U$67";"VIN29";2;"";;;
31;"U$69,U$36,U$70,U$37,U$68,U$71";"GND30";6;"";;;
32;"U$54,U$55";"A523";2;"";;;
33;"U$1";"SFE_LOGO_FLAME_.2";1;"";;;
34;"U$24,U$25";"813";2;"";;;
35;"U$3";"QWIIC_BOARD_MOUNT_HOLES";1;"QWIIC_BOARD_OUTLINEH";;;
36;"U$61,U$60";"A226";2;"";;;
37;"U$77,U$76";"RES33";2;"";;;
38;"J6";"1X07_NO_SILK";1;"";;;
39;"U$62,U$63";"A127";2;"";;;
40;"J4";"1X06_NO_SILK";1;"";;;
41;"U$23,U$21";"712";2;"";;;
42;"U1";"UNO_R3_SHIELD_NOLABELS";1;"ARDUINO UNO";;;
43;"U$6";"3#3V_I2C_PORTS1";1;"";;;
44;"U$38,U$39";"ARF20";2;"";;;
45;"U$7,U$8";"RX5";2;"";;;
46;"U$48,U$49";"3#3V4";2;"";;;
47;"U$32,U$33";"1217";2;"";;;
48;"U$40,U$41";"SDA21";2;"";;;
49;"U$4,U$5";"SHIELD0";2;"";;;
50;"I2C0";"SMT-JUMPER_3_2-NC_TRACE_SILK";1;"";;;
51;"U$22";"I2C0";1;"";;;
52;"U$2";"SFE_LOGO_NAME_FLAME_.1";1;"SFE_LOGO_NAME_FLAME.1_INCH";;;
53;"LOGO1";"OSHW-LOGO-MINI";1;"OSHW-LOGOMINI";;;
